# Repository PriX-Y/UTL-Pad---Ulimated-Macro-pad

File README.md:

# UTL-Pad---Ulimated-Macro-pad

i made this macro with with Statis - HackClub

on this pad is all waht i need for laptop. like
volume, screan bright, mute and more

i be programing this with qmk

i use only kicad and fusion in hardware

there is only case

and qmk site in code

they have 10 switch , 1 oled and 2 rot. encoder with push

there is bom

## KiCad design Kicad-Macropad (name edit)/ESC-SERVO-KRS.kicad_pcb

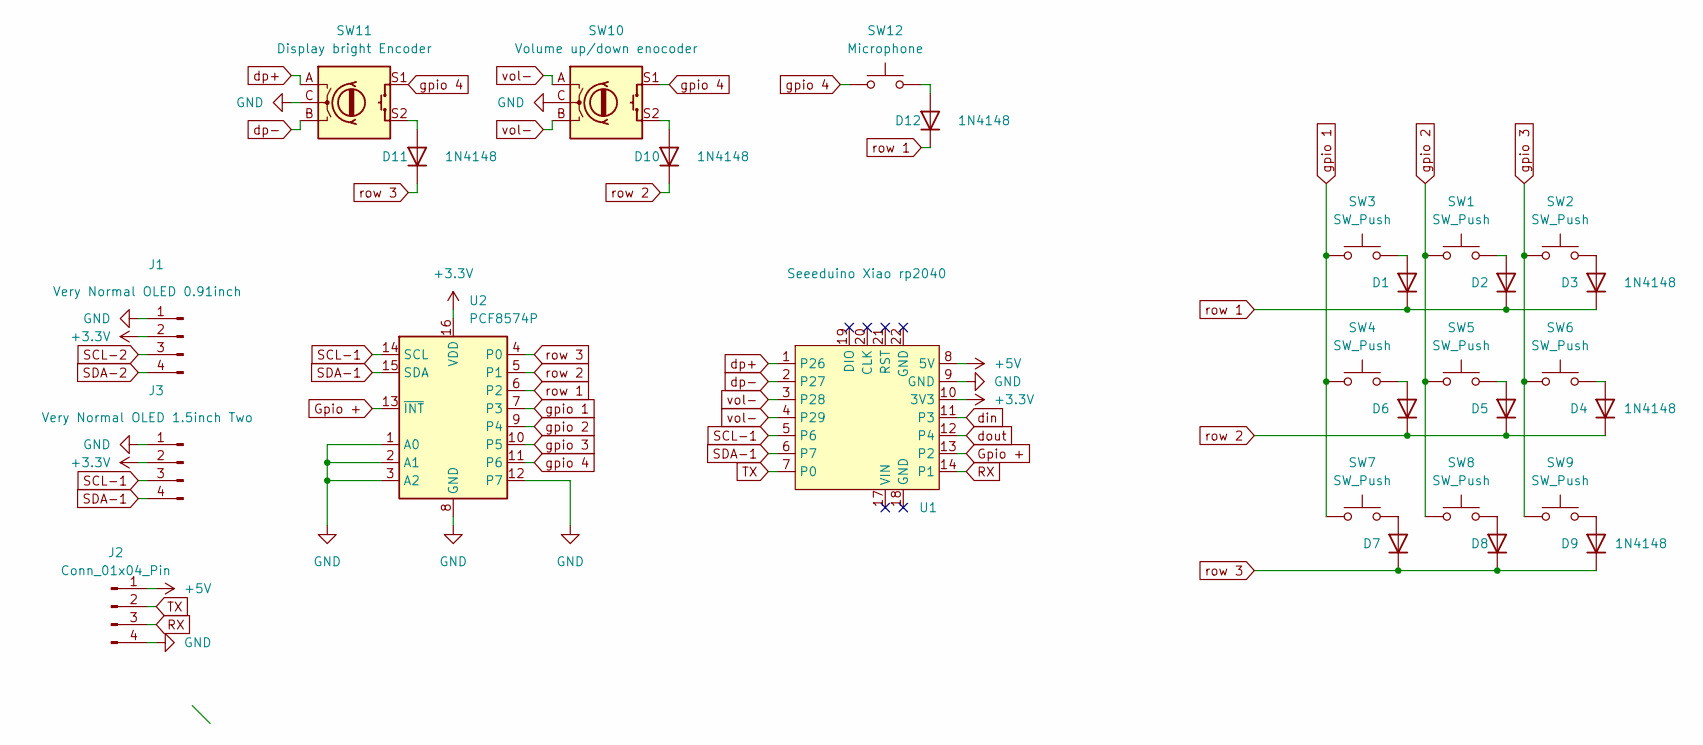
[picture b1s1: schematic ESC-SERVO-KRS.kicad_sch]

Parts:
D1, D2, D3, D4, D5, D6, D7, D8, D9, D10, D11, D12: 1N4148; D_DO-35_SOD27_P7.62mm_Horizontal
J1: Very Normal OLED 0.91inch; PinHeader_1x04_P2.54mm_Vertical
J2: Conn_01x04_Pin; PinHeader_1x04_P2.54mm_Vertical
J3: Very Normal OLED 1.5inch Two; PinHeader_1x04_P2.54mm_Vertical
SW1, SW2, SW3, SW4, SW5, SW6, SW7, SW8, SW9: SW_Push; SW_Cherry_MX_1.00u_PCB
SW10: Volume up/down enocoder; RotaryEncoder_Alps_EC11E-Switch_Vertical_H20mm
SW11: Display bright Encoder; RotaryEncoder_Alps_EC11E-Switch_Vertical_H20mm
SW12: Microphone; SW_Cherry_MX_1.00u_PCB
U1: Seeeduino Xiao rp2040; Xiao_rp2040_ACH
U2: PCF8574P; DIP-16_W7.62mm

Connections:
+3.3V: J1.2, J3.2, U1.10 (3V3), U2.16 (VDD)
+5V: J2.1, U1.8 (5V)
GND: J1.1, J2.4, J3.1, SW10.C, SW11.C, U1.9 (GND), U2.1 (A0), U2.2 (A1), U2.3 (A2), U2.8 (GND), U2.12 (P7)
Gpio +: U1.13 (P2), U2.13 (~INT)
unnamed: D1.2 (A), SW3.2
unnamed: D2.2 (A), SW1.2
unnamed: D3.2 (A), SW2.2
unnamed: D4.2 (A), SW6.2
unnamed: D5.2 (A), SW5.2
unnamed: D6.2 (A), SW4.2
unnamed: D7.2 (A), SW7.2
unnamed: D8.2 (A), SW8.2
unnamed: D9.2 (A), SW9.2
unnamed: D10.2 (A), SW10.S2
unnamed: D11.2 (A), SW11.S2
unnamed: D12.2 (A), SW12.2
RX: J2.3, U1.14 (P1)
SCL-1: J3.3, U1.5 (P6), U2.14 (SCL)
SCL-2: J1.3
SDA-1: J3.4, U1.6 (P7), U2.15 (SDA)
SDA-2: J1.4
TX: J2.2, U1.7 (P0)
din: U1.11 (P3)
dout: U1.12 (P4)
dp+: SW11.A, U1.1 (P26)
dp-: SW11.B, U1.2 (P27)
gpio 1: SW3.1, SW4.1, SW7.1, U2.7 (P3)
gpio 2: SW1.1, SW5.1, SW8.1, U2.9 (P4)
gpio 3: SW2.1, SW6.1, SW9.1, U2.10 (P5)
gpio 4: SW10.S1, SW11.S1, SW12.1, U2.11 (P6)
row 1: D1.1 (K), D2.1 (K), D3.1 (K), D12.1 (K), U2.6 (P2)
row 2: D4.1 (K), D5.1 (K), D6.1 (K), D10.1 (K), U2.5 (P1)
row 3: D7.1 (K), D8.1 (K), D9.1 (K), D11.1 (K), U2.4 (P0)
vol-: SW10.A, SW10.B, U1.3 (P28), U1.4 (P29)

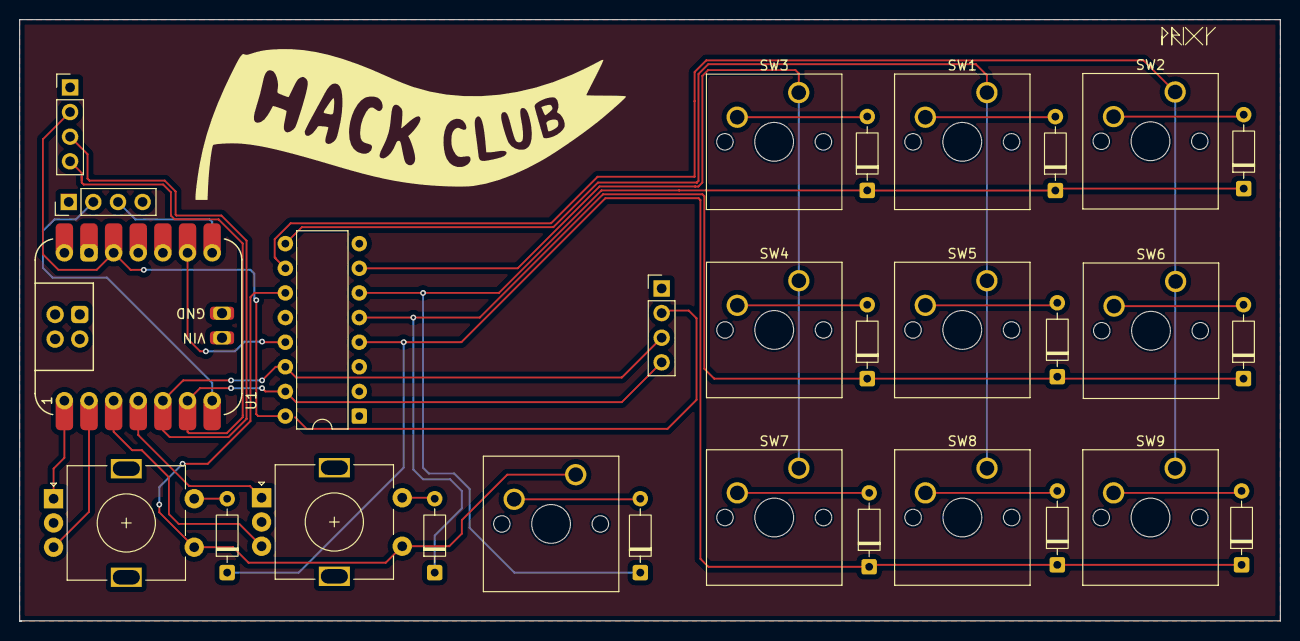
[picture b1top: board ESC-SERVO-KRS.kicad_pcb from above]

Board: 2 copper layers, 130.0 x 62.0 mm, 29 parts (0 on the bottom side), 30 nets.

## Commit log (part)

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2026-04-15 Enhance README with project details and images
    Added project description and images to README.
2026-04-15 Update README with hardware component information
    Added details about hardware components used.
2026-04-15 Update README with image and BOM information
    Added an image and a note about the BOM.
2026-04-19 Update README with images and hardware tools
    Added images and updated hardware tools used.
2026-04-19 Rename C+ Frimware.txt to C+ Frimware.c
2026-04-19 Rename C++ Firmware file from .c to .cpp
